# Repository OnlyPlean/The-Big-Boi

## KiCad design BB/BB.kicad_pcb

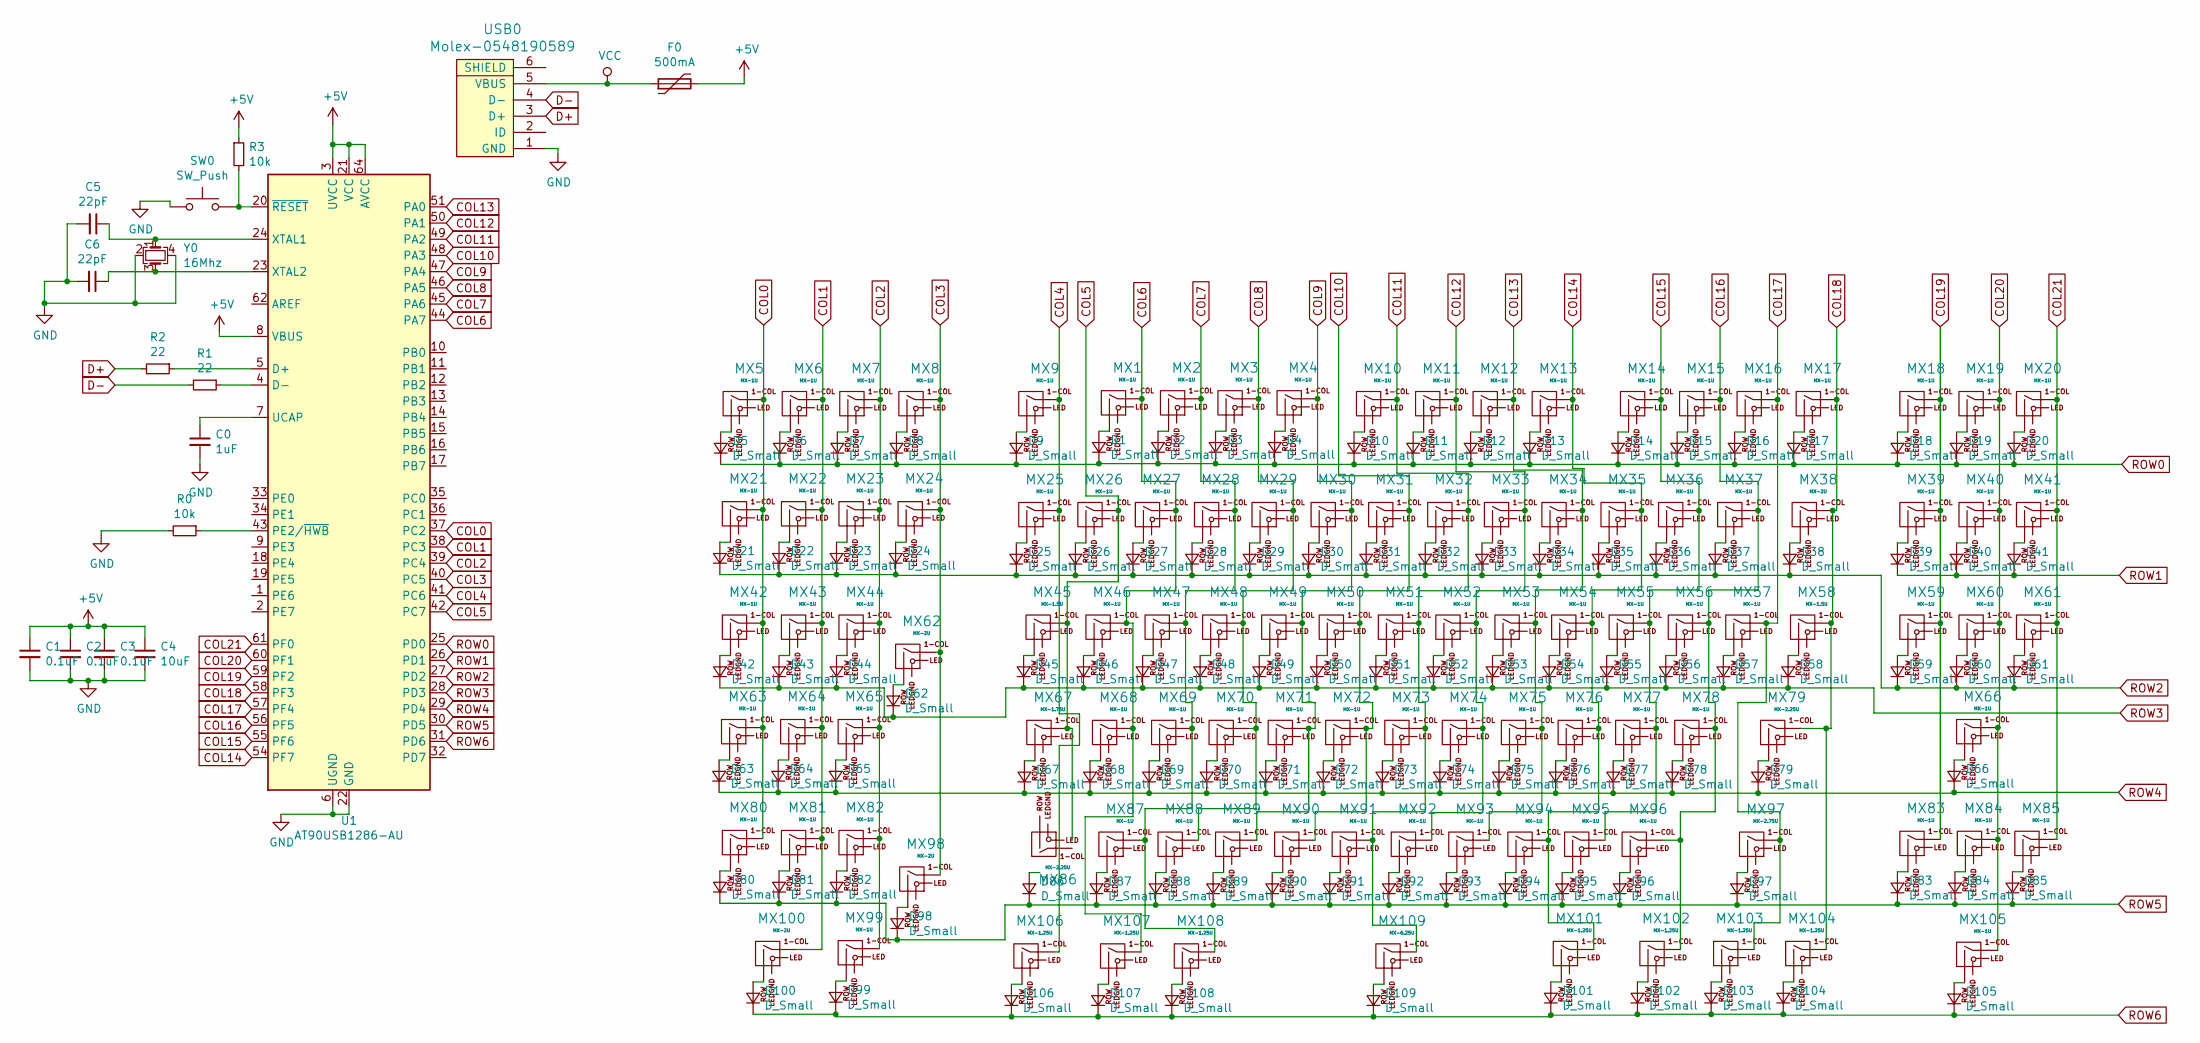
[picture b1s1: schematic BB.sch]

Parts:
C0: 1uF; C_0805_2012Metric
C1, C2, C3: 0.1uF; C_0805_2012Metric
C4: 10uF; C_0805_2012Metric
C5, C6: 22pF; C_0805_2012Metric
D1, D2, D3, D4, D5, D6, D7, D8, D9, D10, D11, D12, D13, D14, D15, D16, D17, D18, D19, D20, D21, D22, D23, D24, D25, D26, D27, D28, D29, D30, D31, D32, D33, D34, D35, D36, D37, D38, D39, D40, D41, D42, D43, D44, D45, D46, D47, D48, D49, D50, D51, D52, D53, D54, D55, D56, D57, D58, D59, D60, D61, D62, D63, D64, D65, D66, D67, D68, D69, D70, D71, D72, D73, D74, D75, D76, D77, D78, D79, D80, D81, D82, D83, D84, D85, D86, D87, D88, D89, D90, D91, D92, D93, D94, D95, D96, D97, D98, D99, D100, D101, D102, D103, D104, D105, D106, D107, D108, D109: D_Small; D_SOD-123
F0: 500mA; Fuse_1206_3216Metric
MX1, MX2, MX3, MX4, MX5, MX6, MX7, MX8, MX9, MX10, MX11, MX12, MX13, MX14, MX15, MX16, MX17, MX18, MX19, MX20, MX21, MX22, MX23, MX24, MX25, MX26, MX27, MX28, MX29, MX30, MX31, MX32, MX33, MX34, MX35, MX36, MX37, MX39, MX40, MX41, MX42, MX43, MX44, MX46, MX47, MX48, MX49, MX50, MX51, MX52, MX53, MX54, MX55, MX56, MX57, MX59, MX60, MX61, MX63, MX64, MX65, MX66, MX68, MX69, MX70, MX71, MX72, MX73, MX74, MX75, MX76, MX77, MX78, MX80, MX81, MX82, MX83, MX84, MX85, MX87, MX88, MX89, MX90, MX91, MX92, MX93, MX94, MX95, MX96, MX99, MX105: MX-1U
MX38, MX62, MX98, MX100: MX-2U
MX45, MX58: MX-1.5U
MX67: MX-1.75U
MX79, MX86: MX-2.25U
MX97: MX-2.75U
MX101, MX102, MX103, MX104, MX106, MX107, MX108: MX-1.25U
MX109: MX-6.25U
R0, R3: 10k; R_0805_2012Metric
R1, R2: 22; R_0805_2012Metric
SW0: SW_Push; SKQG-1155865
U1: AT90USB1286-AU; TQFP-64_14x14mm_P0.8mm
USB0: Molex-0548190589
Y0: 16Mhz; Crystal_SMD_3225-4Pin_3.2x2.5mm

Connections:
+5V: C1.1, C2.1, C3.1, C4.1, F0.2, R3.1, U1.3 (UVCC), U1.8 (VBUS), U1.21 (VCC), U1.52 (VCC), U1.64 (AVCC)
COL0: MX5.1 (COL), MX21.1 (COL), MX42.1 (COL), MX63.1 (COL), MX80.1 (COL), U1.37 (PC2)
COL1: MX6.1 (COL), MX22.1 (COL), MX43.1 (COL), MX64.1 (COL), MX81.1 (COL), MX100.1 (COL), U1.38 (PC3)
COL2: MX7.1 (COL), MX23.1 (COL), MX44.1 (COL), MX65.1 (COL), MX82.1 (COL), MX99.1 (COL), U1.39 (PC4)
COL3: MX8.1 (COL), MX24.1 (COL), MX62.1 (COL), MX98.1 (COL), U1.40 (PC5)
COL4: MX9.1 (COL), MX25.1 (COL), MX106.1 (COL), U1.41 (PC6)
COL5: MX26.1 (COL), MX45.1 (COL), MX67.1 (COL), MX86.1 (COL), U1.42 (PC7)
COL6: MX1.1 (COL), MX27.1 (COL), MX46.1 (COL), MX68.1 (COL), MX107.1 (COL), U1.44 (PA7)
COL7: MX2.1 (COL), MX28.1 (COL), MX47.1 (COL), MX69.1 (COL), MX87.1 (COL), MX108.1 (COL), U1.45 (PA6)
COL8: MX3.1 (COL), MX29.1 (COL), MX48.1 (COL), MX70.1 (COL), MX88.1 (COL), U1.46 (PA5)
COL9: MX4.1 (COL), MX30.1 (COL), MX49.1 (COL), MX71.1 (COL), MX89.1 (COL), U1.47 (PA4)
COL10: MX31.1 (COL), MX50.1 (COL), MX72.1 (COL), MX90.1 (COL), U1.48 (PA3)
COL11: MX10.1 (COL), MX32.1 (COL), MX51.1 (COL), MX73.1 (COL), MX91.1 (COL), MX109.1 (COL), U1.49 (PA2)
COL12: MX11.1 (COL), MX33.1 (COL), MX52.1 (COL), MX74.1 (COL), MX92.1 (COL), U1.50 (PA1)
COL13: MX12.1 (COL), MX34.1 (COL), MX53.1 (COL), MX75.1 (COL), MX93.1 (COL), U1.51 (PA0)
COL14: MX13.1 (COL), MX35.1 (COL), MX54.1 (COL), MX76.1 (COL), MX94.1 (COL), MX101.1 (COL), U1.54 (PF7)
COL15: MX14.1 (COL), MX36.1 (COL), MX55.1 (COL), MX77.1 (COL), MX95.1 (COL), U1.55 (PF6)
COL16: MX15.1 (COL), MX37.1 (COL), MX56.1 (COL), MX78.1 (COL), MX96.1 (COL), MX102.1 (COL), U1.56 (PF5)
COL17: MX16.1 (COL), MX57.1 (COL), MX97.1 (COL), MX103.1 (COL), U1.57 (PF4)
COL18: MX17.1 (COL), MX38.1 (COL), MX58.1 (COL), MX79.1 (COL), MX104.1 (COL), U1.58 (PF3)
COL19: MX18.1 (COL), MX39.1 (COL), MX59.1 (COL), MX83.1 (COL), U1.59 (PF2)
COL20: MX19.1 (COL), MX40.1 (COL), MX60.1 (COL), MX66.1 (COL), MX84.1 (COL), MX105.1 (COL), U1.60 (PF1)
COL21: MX20.1 (COL), MX41.1 (COL), MX61.1 (COL), MX85.1 (COL), U1.61 (PF0)
D+: R2.2, USB0.3 (D+)
D-: R1.2, USB0.4 (D-)
GND: C0.2, C1.2, C2.2, C3.2, C4.2, C5.2, C6.2, R0.2, SW0.1, U1.6 (UGND), U1.22 (GND), U1.53 (GND), U1.63 (GND), USB0.1 (GND), Y0.2, Y0.4
unnamed: C0.1, U1.7 (UCAP)
unnamed: C5.1, U1.24 (XTAL1), Y0.1
unnamed: C6.1, U1.23 (XTAL2), Y0.3
unnamed: D1.2 (A), MX1.2 (ROW)
unnamed: D2.2 (A), MX2.2 (ROW)
unnamed: D3.2 (A), MX3.2 (ROW)
unnamed: D4.2 (A), MX4.2 (ROW)
unnamed: D5.2 (A), MX5.2 (ROW)
unnamed: D6.2 (A), MX6.2 (ROW)
unnamed: D7.2 (A), MX7.2 (ROW)
unnamed: D8.2 (A), MX8.2 (ROW)
unnamed: D9.2 (A), MX9.2 (ROW)
unnamed: D10.2 (A), MX10.2 (ROW)
unnamed: D11.2 (A), MX11.2 (ROW)
unnamed: D12.2 (A), MX12.2 (ROW)
unnamed: D13.2 (A), MX13.2 (ROW)
unnamed: D14.2 (A), MX14.2 (ROW)
unnamed: D15.2 (A), MX15.2 (ROW)
unnamed: D16.2 (A), MX16.2 (ROW)
unnamed: D17.2 (A), MX17.2 (ROW)
unnamed: D18.2 (A), MX18.2 (ROW)
unnamed: D19.2 (A), MX19.2 (ROW)
unnamed: D20.2 (A), MX20.2 (ROW)
unnamed: D21.2 (A), MX21.2 (ROW)
unnamed: D22.2 (A), MX22.2 (ROW)
unnamed: D23.2 (A), MX23.2 (ROW)
unnamed: D24.2 (A), MX24.2 (ROW)
unnamed: D25.2 (A), MX25.2 (ROW)
unnamed: D26.2 (A), MX26.2 (ROW)
unnamed: D27.2 (A), MX27.2 (ROW)
unnamed: D28.2 (A), MX28.2 (ROW)
unnamed: D29.2 (A), MX29.2 (ROW)
unnamed: D30.2 (A), MX30.2 (ROW)
unnamed: D31.2 (A), MX31.2 (ROW)
unnamed: D32.2 (A), MX32.2 (ROW)
unnamed: D33.2 (A), MX33.2 (ROW)
unnamed: D34.2 (A), MX34.2 (ROW)
unnamed: D35.2 (A), MX35.2 (ROW)
unnamed: D36.2 (A), MX36.2 (ROW)
unnamed: D37.2 (A), MX37.2 (ROW)
unnamed: D38.2 (A), MX38.2 (ROW)
unnamed: D39.2 (A), MX39.2 (ROW)
unnamed: D40.2 (A), MX40.2 (ROW)
unnamed: D41.2 (A), MX41.2 (ROW)
unnamed: D42.2 (A), MX42.2 (ROW)
unnamed: D43.2 (A), MX43.2 (ROW)
unnamed: D44.2 (A), MX44.2 (ROW)
unnamed: D45.2 (A), MX45.2 (ROW)
unnamed: D46.2 (A), MX46.2 (ROW)
unnamed: D47.2 (A), MX47.2 (ROW)
unnamed: D48.2 (A), MX48.2 (ROW)
unnamed: D49.2 (A), MX49.2 (ROW)
unnamed: D50.2 (A), MX50.2 (ROW)
unnamed: D51.2 (A), MX51.2 (ROW)
unnamed: D52.2 (A), MX52.2 (ROW)
unnamed: D53.2 (A), MX53.2 (ROW)
unnamed: D54.2 (A), MX54.2 (ROW)
unnamed: D55.2 (A), MX55.2 (ROW)
unnamed: D56.2 (A), MX56.2 (ROW)
unnamed: D57.2 (A), MX57.2 (ROW)
unnamed: D58.2 (A), MX58.2 (ROW)
unnamed: D59.2 (A), MX59.2 (ROW)
unnamed: D60.2 (A), MX60.2 (ROW)
unnamed: D61.2 (A), MX61.2 (ROW)
unnamed: D62.2 (A), MX62.2 (ROW)
unnamed: D63.2 (A), MX63.2 (ROW)
unnamed: D64.2 (A), MX64.2 (ROW)
unnamed: D65.2 (A), MX65.2 (ROW)
unnamed: D66.2 (A), MX66.2 (ROW)
unnamed: D67.2 (A), MX67.2 (ROW)
unnamed: D68.2 (A), MX68.2 (ROW)
unnamed: D69.2 (A), MX69.2 (ROW)
unnamed: D70.2 (A), MX70.2 (ROW)
unnamed: D71.2 (A), MX71.2 (ROW)
unnamed: D72.2 (A), MX72.2 (ROW)
unnamed: D73.2 (A), MX73.2 (ROW)
unnamed: D74.2 (A), MX74.2 (ROW)
unnamed: D75.2 (A), MX75.2 (ROW)
unnamed: D76.2 (A), MX76.2 (ROW)
unnamed: D77.2 (A), MX77.2 (ROW)
unnamed: D78.2 (A), MX78.2 (ROW)
unnamed: D79.2 (A), MX79.2 (ROW)
unnamed: D80.2 (A), MX80.2 (ROW)
unnamed: D81.2 (A), MX81.2 (ROW)
unnamed: D82.2 (A), MX82.2 (ROW)
unnamed: D83.2 (A), MX83.2 (ROW)
unnamed: D84.2 (A), MX84.2 (ROW)
unnamed: D85.2 (A), MX85.2 (ROW)
unnamed: D86.2 (A), MX86.2 (ROW)
unnamed: D87.2 (A), MX87.2 (ROW)
unnamed: D88.2 (A), MX88.2 (ROW)
unnamed: D89.2 (A), MX89.2 (ROW)
unnamed: D90.2 (A), MX90.2 (ROW)
unnamed: D91.2 (A), MX91.2 (ROW)
unnamed: D92.2 (A), MX92.2 (ROW)
unnamed: D93.2 (A), MX93.2 (ROW)
unnamed: D94.2 (A), MX94.2 (ROW)
unnamed: D95.2 (A), MX95.2 (ROW)
unnamed: D96.2 (A), MX96.2 (ROW)
unnamed: D97.2 (A), MX97.2 (ROW)
unnamed: D98.2 (A), MX98.2 (ROW)
unnamed: D99.2 (A), MX99.2 (ROW)
unnamed: D100.2 (A), MX100.2 (ROW)
unnamed: D101.2 (A), MX101.2 (ROW)
unnamed: D102.2 (A), MX102.2 (ROW)
unnamed: D103.2 (A), MX103.2 (ROW)
unnamed: D104.2 (A), MX104.2 (ROW)
unnamed: D105.2 (A), MX105.2 (ROW)
unnamed: D106.2 (A), MX106.2 (ROW)
unnamed: D107.2 (A), MX107.2 (ROW)
unnamed: D108.2 (A), MX108.2 (ROW)
unnamed: D109.2 (A), MX109.2 (ROW)
unnamed: R0.1, U1.43 (PE2/~HWB)
unnamed: R1.1, U1.4 (D-)
unnamed: R2.1, U1.5 (D+)
unnamed: R3.2, SW0.2, U1.20 (~RESET)
ROW0: D1.1 (K), D2.1 (K), D3.1 (K), D4.1 (K), D5.1 (K), D6.1 (K), D7.1 (K), D8.1 (K), D9.1 (K), D10.1 (K), D11.1 (K), D12.1 (K), D13.1 (K), D14.1 (K), D15.1 (K), D16.1 (K), D17.1 (K), D18.1 (K), D19.1 (K), D20.1 (K), U1.25 (PD0)
ROW1: D39.1 (K), D40.1 (K), D41.1 (K), U1.26 (PD1)
ROW2: D21.1 (K), D22.1 (K), D23.1 (K), D24.1 (K), D25.1 (K), D26.1 (K), D27.1 (K), D28.1 (K), D29.1 (K), D30.1 (K), D31.1 (K), D32.1 (K), D33.1 (K), D34.1 (K), D35.1 (K), D36.1 (K), D37.1 (K), D38.1 (K), D59.1 (K), D60.1 (K), D61.1 (K), U1.27 (PD2)
ROW3: D42.1 (K), D43.1 (K), D44.1 (K), D45.1 (K), D46.1 (K), D47.1 (K), D48.1 (K), D49.1 (K), D50.1 (K), D51.1 (K), D52.1 (K), D53.1 (K), D54.1 (K), D55.1 (K), D56.1 (K), D57.1 (K), D58.1 (K), D62.1 (K), U1.28 (PD3)
ROW4: D63.1 (K), D64.1 (K), D65.1 (K), D66.1 (K), D67.1 (K), D68.1 (K), D69.1 (K), D70.1 (K), D71.1 (K), D72.1 (K), D73.1 (K), D74.1 (K), D75.1 (K), D76.1 (K), D77.1 (K), D78.1 (K), D79.1 (K), U1.29 (PD4)
ROW5: D80.1 (K), D81.1 (K), D82.1 (K), D83.1 (K), D84.1 (K), D85.1 (K), D86.1 (K), D87.1 (K), D88.1 (K), D89.1 (K), D90.1 (K), D91.1 (K), D92.1 (K), D93.1 (K), D94.1 (K), D95.1 (K), D96.1 (K), D97.1 (K), D98.1 (K), U1.30 (PD5)
ROW6: D99.1 (K), D100.1 (K), D101.1 (K), D102.1 (K), D103.1 (K), D104.1 (K), D105.1 (K), D106.1 (K), D107.1 (K), D108.1 (K), D109.1 (K), U1.31 (PD6)
VCC: F0.1, USB0.5 (VBUS)

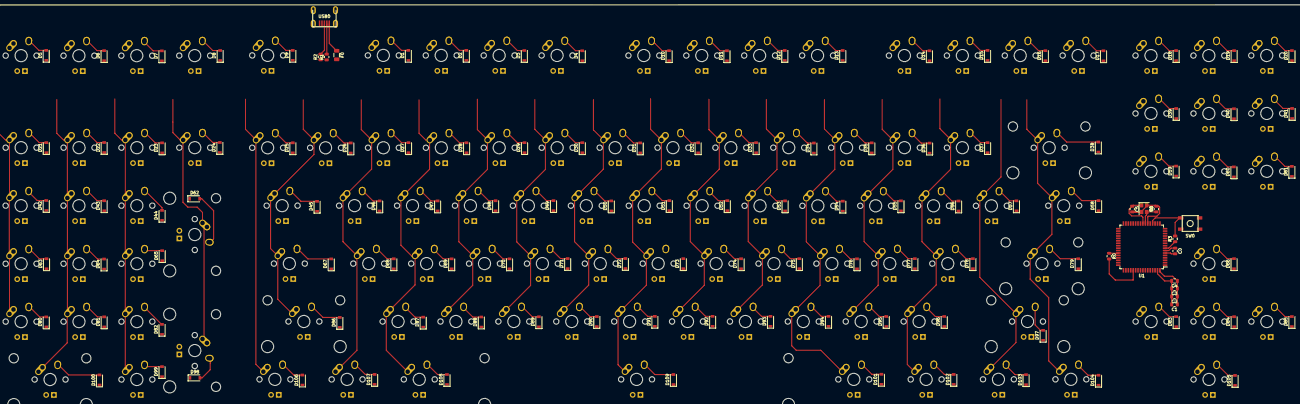
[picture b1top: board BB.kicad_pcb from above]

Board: 2 copper layers, 234 parts (0 on the bottom side), 150 nets.

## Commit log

2019-04-11 Initial Files
2019-04-11 Add submodules
2019-04-11 Adding Keyboard Footprint
2019-04-11 MCU Without Switches
2019-04-11 USB Molex
2019-04-11 Numpad Switches Added
2019-04-11 All Switches In Place
    No diodes yet, waiting for 2-1 diode schematic
2019-04-11 All Switches in place with Diodes
2019-04-11 Columns Wired
2019-04-11 Rows and Columns Connected Up
2019-04-11 Finished Schematic
2019-04-11 Generated Netlist
    Sand Crawler
2019-04-11 Half Switches in Place on PCB
    Fixed issue on switch 62 2u
2019-04-11 4 rows placed
2019-04-11 5 Rows Done
    Fixed 2u key footprint on key 38
2019-04-11 Rows Done
    Excluding Right Pad
2019-04-11 All Switches Placed
    Diodes on Side
2019-04-11 All Componenets in Place on PCB
    No routing, temporary MCU placement
2019-04-11 Change Page Size
    Ready for Routing
2019-04-13 Outline Finished
2019-04-13 Checkpoint Before Routing
    Calm before the storm
2019-04-13 Rows Done
    Main Columns
2019-04-13 Finished Numpad and Alphas
    Fixed numpad endings
2019-04-13 Diodes with Pads
    Excluding shift and keys larger than 2u on the alphas
2019-04-19 MCU Wired
    No rows or colomns
2019-04-19 Some Columns
